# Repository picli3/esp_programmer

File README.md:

</br>
[certification OSHW](https://certification.oshwa.org/pe000001.html)

---
# ESP32 Prog Lite

This module was designed to optimize the programming of ESP32 devices in production environments. It emerged as a solution to a common problem: the need to efficiently and cost-effectively program electronic products that don't require a USB port for final operation.

|             |                 |
|:------------:|:----------------:|
|          ||

## The USB problem in production

For devices that run on alkaline batteries or are programmed only once at the factory, a USB connector and its integrated serial converter, such as the popular CP2102N, represent an unnecessary cost. In mass production, these components add up to a considerable expense. For example, in a production run of 1,000 units, a converter at $2 USD per piece increases the total cost by $2,000 USD, not including the other associated components and the space they take up on the board.

In a real-world case, a customer looking to update their PCB design had a USB-C converter on their board. By eliminating these circuits and offering our solution, which uses Pogo-Pin clips, we were able to significantly reduce their costs and production time.

## A simple and efficient design

Our main objective was to simplify the programming process, making it as small and efficient as possible. We were inspired by the **ESP-programmer**, a device known for its JTAG programming and debugging capabilities. However, our goal was not to replicate all of its features, but rather to create a minimalist tool focused exclusively on production programming that would allow for seamless integration and rapid adoption on any assembly line.

This approach has allowed us to develop a programmer that offers a low-cost, high-performance solution for mass production of ESP32-based products.

## Why choose this programmer?

* **Cost savings:** Eliminates the need for integrated USB-to-serial converters on each board, dramatically reducing unit costs in mass production.

* **Space optimization:** Its compact design frees up valuable PCB space, ideal for products with size constraints.

* **Production efficiency:** Enables quick and easy programming using Pogo-Pin connectors, streamlining the manufacturing process.

## BOM
| **#**     | **Reference**     | **Description**                                                                                                           | **Qty**   | **Part #**                | **Manufacturer**              | **LCSC**  |
|-------    |---------------    |------------------------------------------------------------------------------------------------------------------------   |---------  |-----------------------    |---------------------------    |---------- |
| 1         | C3                | 10V 4.7uF X5R ±10% 0603 Multilayer Ceramic Capacitors MLCC - SMD/SMT ROHS                                                 | 1         | CL10A475KP8NNNC           | Samsung Electro-Mechanics     | C1705     |
| 2         | C4                | 50V 100nF X7R ±10% 0603 Multilayer Ceramic Capacitors MLCC - SMD/SMT ROHSr                                                | 1         | CC0603KRX7R9BB104         | YAGEO                         | C14663    |
| 3         | C1,C2             | 50V 1uF X7R ±10% 0805 Multilayer Ceramic Capacitors MLCC - SMD/SMT ROHS                                                   | 2         | CL21B105KBFNNNE           | Samsung Electro-Mechanics     | C28323    |
| 4         | J2                | Right Angle Pin Header 2.5mm 6mm 6P -40℃~+105℃ 2.54mm 2 Black Brass 2x3P Push-Pull,P=2.54mm Pin Headers ROHS              | 1         | PH2.54-07-03PWS           | XUNPU                         | C7501617  |
| 5         | J1                | USB 2.0-only 14P Type-C Receptacle connector                                                                              | 1         | TYPE-C 16PIN 2MD(073)     | SHOU HAN                      | C2765186  |
| 6         | D1,D2             | 25mA 80mcd~220mcd Independent Diode 615nm~630nm -30℃~+85℃ Red 130° 65mW 1.6V~2.6V 0603 LED Indication - Discrete ROHS     | 2         | NCD0603R1                 | NATIONSTAR                    | C84263    |
| 7         | U1                | USB to UART QFN-28-EP(5x5) USB Converters ROHS                                                                            | 1         | CP2102N-A02-GQFN28R       | SILICON LABS                  | C964632   |
| 8         | U2                | 600mA low dropout linear regulator, with enable pin, 3.8V-6V input voltage range, 3.3V fixed positive output, SOT-23-5    | 1         | AP2112K-3.3TRG1           | Diodes Incorporated           | C51118    |
| 9         | Q1,Q2             | 40V 200mW 100@10mA,1V 200mA NPN SOT-23 Bipolar (BJT) ROHS                                                                 | 2         | MMBT3904                  | TWGMC                         | C727127   |
| 10        | R1,R2             | 100mW Thick Film Resistors 75V ±1% ±400ppm/℃ 10Ω 0603 Chip Resistor - Surface Mount ROHS                                  | 2         | 0603WAF100JT5E            | UNI-ROYAL                     | C22859    |
| 11        | R3                | 100mW Thick Film Resistor 75V ±100ppm/℃ ±1% 22.1kΩ 0603 Chip Resistor - Surface Mount ROHS                                | 1         | RC0603FR-0722K1L          | YAGEO                         | C137768   |
| 12        | R4                | 100mW Thick Film Resistor 75V ±100ppm/℃ ±1% 47.5kΩ 0603 Chip Resistor - Surface Mount ROHS                                | 1         | RC0603FR-0747K5L          | YAGEO                         | C137715   |
| 13        | R5                | Thin Film Resistors - SMD 1K ohm 1% 1/10W                                                                                 | 1         | ARG03FTC1001              | Viking                        | C217840   |
| 14        | R6,R7             | Thick Film Resistors - SMD 330 Ohms 100mW 0603 1%                                                                         | 2         | RC0603FR-07330RL          | YAGEO                         | C105881   |
| 15        | R8,R9             | 100mW ±100ppm/℃ ±1% 10kΩ 0603 Chip Resistor - Surface Mount ROHS                                                          | 2         | RMC16K103FTP              | KAMAYA                        | C323556   |
| 16        | R10,R11           | 100mW Thick Film Resistor 75V ±100ppm/℃ ±1% 5.1kΩ 0603 Chip Resistor - Surface Mount ROHS                                 | 2         | 0603WAF5101T5E            | UNI-ROYAL                     | C23186    |

## Generate panel

To do this it is required [Kikit](https://github.com/yaqwsx/KiKit?tab=readme-ov-file)

```sh
kikit panelize \
    --layout 'grid; rows: 6; cols: 2; space: 2mm' \
    --tabs 'fixed; width: 3mm; vcount: 2' \
    --cuts 'mousebites; drill: 0.5mm; spacing: 1mm; offset: 0.2mm; prolong: 0.5mm' \
    --framing 'railstb; width: 5mm; space: 3mm;' \
    --tooling '3hole; hoffset: 2.5mm; voffset: 2.5mm; size: 1.5mm' \
    --fiducials '3fid; hoffset: 5mm; voffset: 2.5mm; coppersize: 2mm; opening: 1mm;' \
    --text 'simple; text: MaykolRey.com; anchor: mt; voffset: 2.5mm; hjustify: center; vjustify: center;' \
    --text2 'simple; text: Created on {date}; anchor: mb; voffset: -2.5mm; hjustify: center; vjustify: center;' \
    --post 'millradius: 1mm' \
    ESP_32_Programer.kicad_pcb panel/panel.kicad_pcb
```
## Licence

Author: Maykol Rey

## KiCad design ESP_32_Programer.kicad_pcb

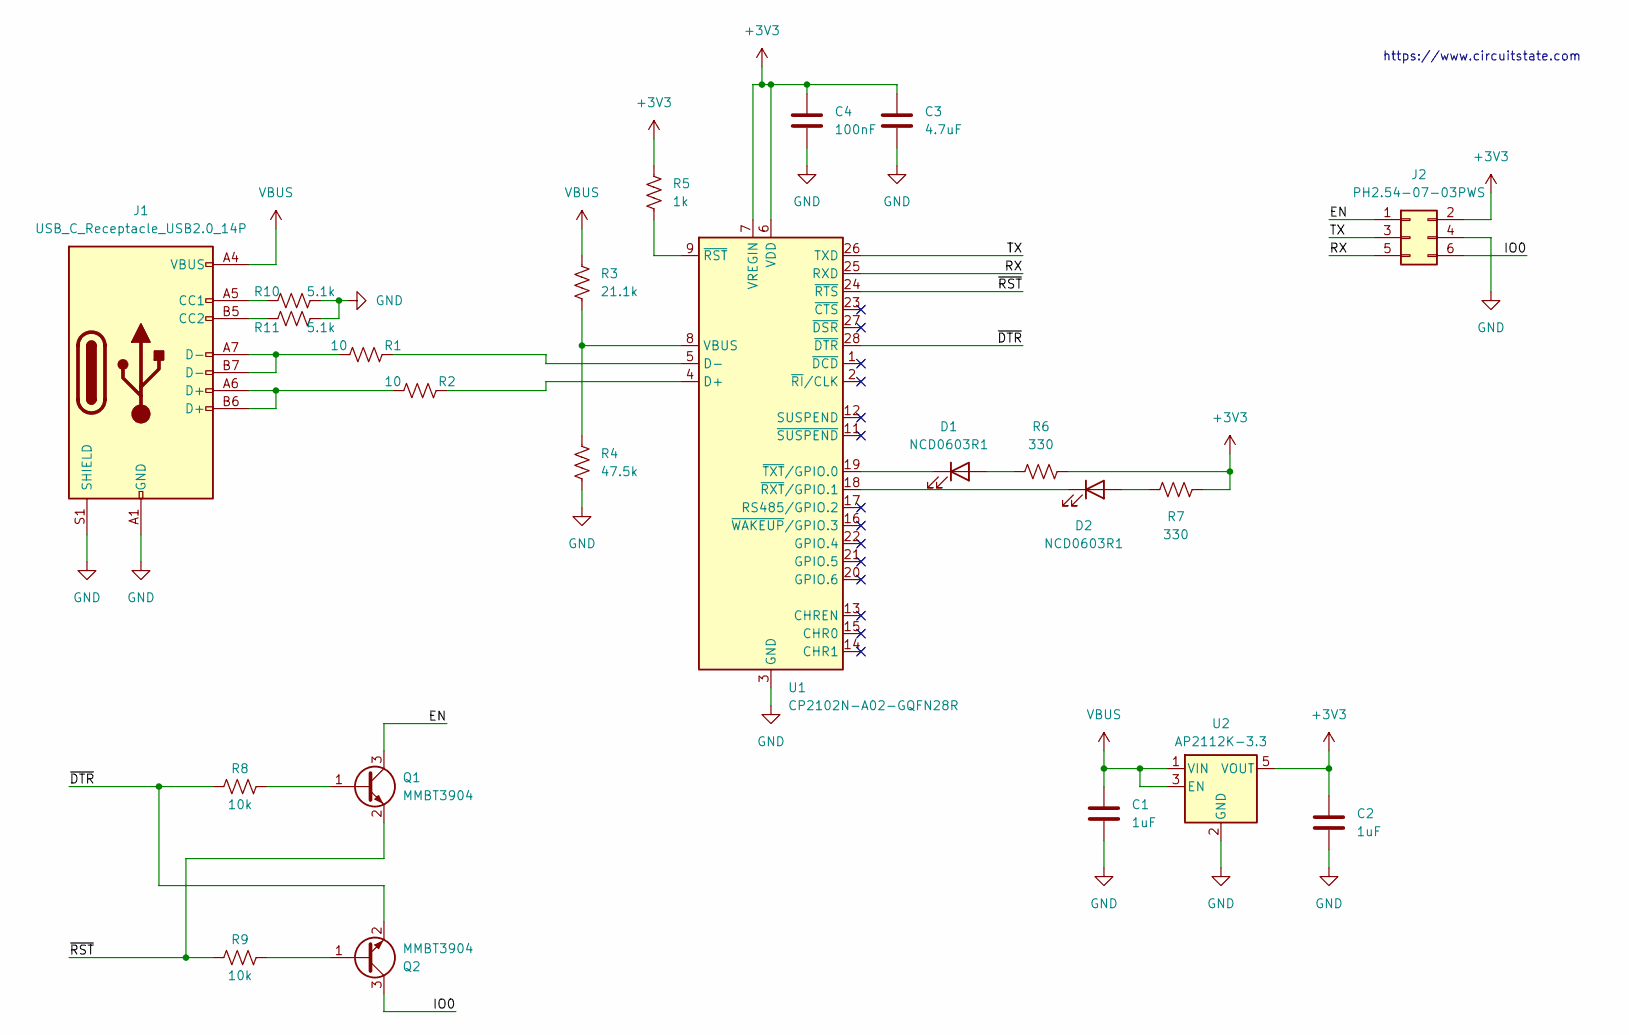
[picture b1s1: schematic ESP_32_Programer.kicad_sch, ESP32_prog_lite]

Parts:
C1, C2: 1uF; C_0805_2012Metric; Part # CL21B105KBFNNNE; LCSC C28323
C3: 4.7uF; C_0603_1608Metric; Part # CL10A475KP8NNNC; LCSC C1705
C4: 100nF; C_0603_1608Metric; Part # CC0603KRX7R9BB104; LCSC C14663
D1, D2: NCD0603R1; LED_0603_1608Metric; Part # NCD0603R1; LCSC C84263
J1: USB_C_Receptacle_USB2.0_14P; USB_C_Receptacle_GCT_USB4105-xx-A_16P_TopMnt_Horizontal; Part # TYPE-C 16PIN 2MD(073); LCSC C2765186
J2: PH2.54-07-03PWS; PinHeader_2x03_P2.54mm_Horizontal; Part # PH2.54-07-03PWS; LCSC C7501617
Q1, Q2: MMBT3904; SOT-23; Part # MMBT3904; LCSC C727127
R1, R2: 10; R_0603_1608Metric; Tolerance ±1%; Part # 0603WAF100JT5E; LCSC C22859
R3: 21.1k; R_0603_1608Metric; Tolerance ±1%; Part # RC0603FR-0722K1L; LCSC C137768
R4: 47.5k; R_0603_1608Metric; Tolerance ±1%; Part # RC0603FR-0747K5L; LCSC C137715
R5: 1k; R_0603_1608Metric; Part # ARG03FTC1001; LCSC C217840
R6, R7: 330; R_0603_1608Metric; Part # RC0603FR-07330RL; LCSC C105881
R8, R9: 10k; R_0603_1608Metric; Tolerance ±1%; Part # RMC16K103FTP; LCSC C323556
R10, R11: 5.1k; R_0603_1608Metric; Tolerance ±1%; Part # 0603WAF5101T5E; LCSC C23186
U1: CP2102N-A02-GQFN28R; QFN-28-1EP_5x5mm_P0.5mm_EP3.35x3.35mm; Part # CP2102N-A02-GQFN28R; LCSC C964632
U2: AP2112K-3.3; SC-74A-5_1.55x2.9mm_P0.95mm; Part # AP2112K-3.3TRG1; LCSC C51118

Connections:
+3V3: C2.1, C3.1, C4.1, J2.2, R5.1, R6.2, R7.2, U1.6 (VDD), U1.7 (VREGIN), U2.5 (VOUT)
/EN: J2.1, Q1.3 (C)
/IO0: J2.6, Q2.3 (C)
/RX: J2.5, U1.25 (RXD)
/TX: J2.3, U1.26 (TXD)
/~DTR: Q2.2 (E), R8.1, U1.28 (~DTR)
/~RST: Q1.2 (E), R9.1, U1.24 (~RTS)
GND: C1.2, C2.2, C3.2, C4.2, J1.A1 (GND), J1.A12 (GND), J1.B1 (GND), J1.B12 (GND), J1.S1 (SHIELD), J2.4, R4.2, R10.2, R11.2, U1.3 (GND), U1.29 (GND), U2.2 (GND)
unnamed: D1.2 (A), R6.1
unnamed: D1.1 (K), U1.19 (~TXT/GPIO.0)
unnamed: D2.2 (A), R7.1
unnamed: D2.1 (K), U1.18 (~RXT/GPIO.1)
unnamed: J1.A5 (CC1), R10.1
unnamed: J1.B5 (CC2), R11.1
unnamed: J1.A6 (D+), J1.B6 (D+), R2.1
unnamed: J1.A7 (D-), J1.B7 (D-), R1.1
unnamed: Q1.1 (B), R8.2
unnamed: Q2.1 (B), R9.2
unnamed: R2.2, U1.4 (D+)
unnamed: R1.2, U1.5 (D-)
unnamed: R3.2, R4.1, U1.8 (VBUS)
unnamed: R5.2, U1.9 (~RST)
VBUS: C1.1, J1.A4 (VBUS), J1.A9 (VBUS), J1.B4 (VBUS), J1.B9 (VBUS), R3.1, U2.1 (VIN), U2.3 (EN)

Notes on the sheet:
https://www.circuitstate.com

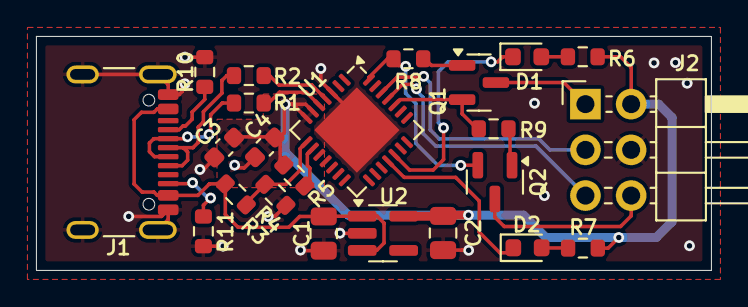
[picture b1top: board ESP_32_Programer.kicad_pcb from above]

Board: 2 copper layers, 37.5 x 13.0 mm, 23 parts (0 on the bottom side), 23 nets.

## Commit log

2025-06-18 completando esquematico
2025-06-23 completando el diseño de la pcb
2025-06-24 corrigiendo error en USB y completando BOM
2025-06-24 completando PCB
2025-07-12 completando version fabricada en PCBWay
2025-09-19 actualizando documentacion generando version v1.1.0
2025-09-19 agregando script para panel
2025-09-19 Rename .env to env
2025-09-19 add licence
2025-09-20 actualizando README agregando BOM
